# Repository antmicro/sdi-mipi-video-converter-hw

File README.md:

# SDI-MIPI Video Converter

Copyright (c) 2022-2025 [Antmicro](https://www.antmicro.com)

## Overview

This repository contains open hardware design files for a video accessory based on the [Lattice CrossLink-NX](https://www.latticesemi.com/Products/FPGAandCPLD/CrossLink-NX) FPGA which allows to connect multiple video streams from SDI or CSI inputs, process it on-board and export with CSI output.

The design files were prepared in KiCad 9.x.

## Repository structure

The main repository directory contains KiCad PCB project files, a [LICENSE](LICENSE), and a README.
The remaining files are stored in the following directories:

* `img` - contains graphics for this README

## Key Features

* LIFCL-40-9BG256C Lattice CrossLink-NX FPGA
* 3G SDI Input implemented with Semtech GS2971A deserializer 
* 3G SDI Loopback output implemented with Semtech GS2988 cable driver
* 3x4 CSI interfaces split 2/1 between two Antmicro 50-pin FFC connectors 
* 2Gbit (128Mx16) DDR3L DRAM

The board can be powered from either USB or Antmicro's 50-pin FFC connector.

Antmicro's 50-pin FFC connector is electrically compatible with several boards created by Antmicro, such as:
 
* [Jetson Nano/TX2 NX/Xavier NX Baseboard](https://github.com/antmicro/jetson-nano-baseboard)
* [OV9281 Dual Camera Board](https://github.com/antmicro/ov9281-camera-board)
* [HDMI-MIPI bridge](https://github.com/antmicro/hdmi-mipi-bridge)

## License

[Apache-2.0](LICENSE)

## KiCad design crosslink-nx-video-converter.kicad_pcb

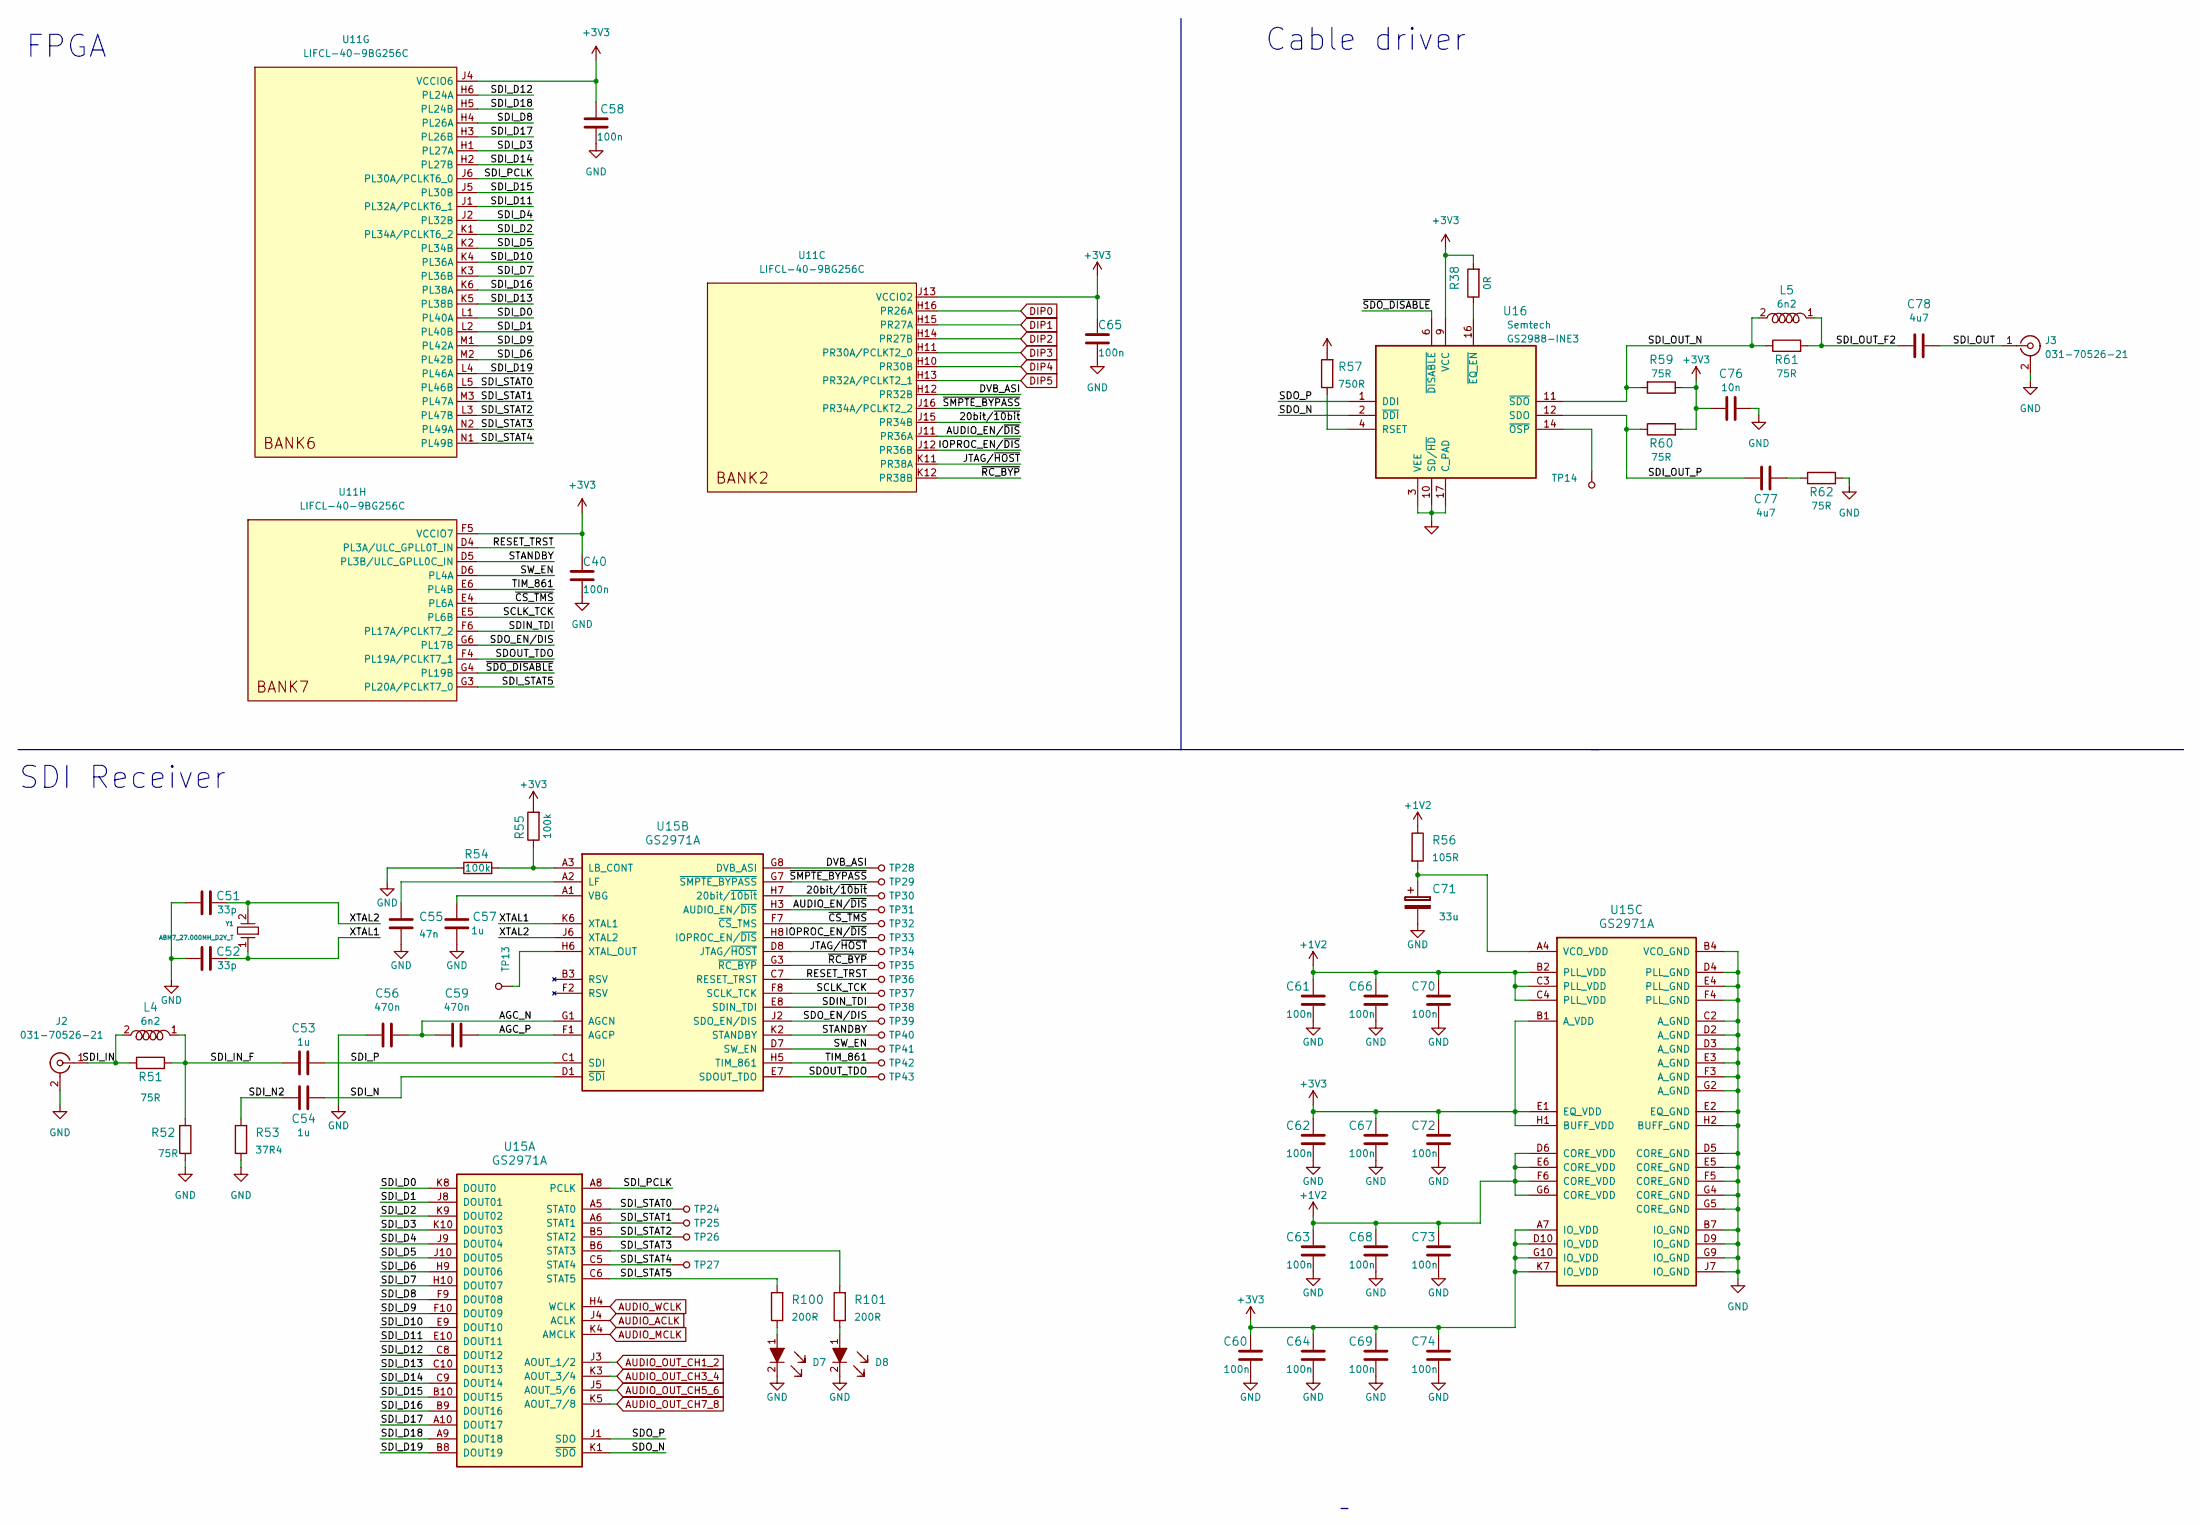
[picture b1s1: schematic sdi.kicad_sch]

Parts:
C40, C58, C60, C61, C62, C63, C64, C65, C66, C67, C68, C69, C70, C72, C73, C74: C_100n_0402; 0402-cap; MPN GRM155R61H104KE14D
C51, C52: C_33p_0402; 0402-cap; MPN MC0402N330J500CT
C53, C54, C57: C_1u_0402; 0402-cap; MPN C1005X6S1A105K050BC
C55: C_47n_0402; 0402-cap; MPN MC0402X473K160CT
C56, C59: C_470n_0402; 0402-cap; MPN C1005X5R1E474M050BB
C71: C_33u_0603; 0603-cap; MPN F980G336MMA
C76: C_10n_0402; 0402-cap; MPN 04025G103ZAT2A
C77, C78: C_4u7_0402; 0402-cap; MPN GRM155R61A475MEAAD
D7, D8: LTST-C190GKT; LED_0603; MPN LTST-C190GKT
J2, J3: 031-70526-21; BNC_Edge_Conn; MPN 031-70526-21
L4, L5: L_0402_6n2; 0402-cap; MPN LQW15AN6N2C00D
R38: R_0R_0402; 0402-res; MPN ERJ2GE0R00X
R51, R52, R59, R60, R61, R62: R_75R_0402; 0402-res; MPN RC0402FR-0775RL
R53: R_37R4_0402; 0402-res; MPN MCWR04X37R4FTL
R54, R55: R_100k_0402; 0402-res; MPN CRCW0402100KFKEDHP
R56: R_105R_0402; 0402-res; MPN MC00625W04021105R
R57: R_750R_0402; 0402-res; MPN RC0402FR-07750RL
R100, R101: R_200R_0603; 0603-res; MPN ERJ-UP3F2000V
TP13, TP14, TP24, TP25, TP26, TP27, TP28, TP29, TP30, TP31, TP32, TP33, TP34, TP35, TP36, TP37, TP38, TP39, TP40, TP41, TP42, TP43: TP_SMD_0_75MM; Testpoint_smd_0_75mm
U11: LIFCL-40-9BG256C; BGA-256_16x16_14.0x14.0mm; MPN LIFCL-40-9BG256C
U15: GS2971A; BGA100_11x11mm; MPN GS2971A
U16: GS2988; QFN-16_EP_4x4_Pitch0.65mm; MPN GS2988-INE3
Y1: ABM7_27.000MH_D2Y_T; ABM7_OSC; MPN ABM7-27.000MHZ-D2Y-T

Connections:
+1V2: C61.1, C63.1, C66.1, C68.1, C70.1, C73.1, R56.1, U15.B2 (PLL_VDD), U15.C3 (PLL_VDD), U15.C4 (PLL_VDD), U15.D6 (CORE_VDD), U15.E6 (CORE_VDD), U15.F6 (CORE_VDD), U15.G6 (CORE_VDD); also elsewhere on the board
/SDI/20bit/~10bit: TP30.1, U11.J15 (PR34B), U15.H7 (20bit/~10bit)
/SDI/AGC_N: C56.2, C59.1, U15.G1 (AGCN)
/SDI/AGC_P: C59.2, U15.F1 (AGCP)
/SDI/AUDIO_EN/~DIS: TP31.1, U11.J11 (PR36A), U15.H3 (AUDIO_EN/~DIS)
/SDI/DVB_ASI: TP28.1, U11.H12 (PR32B), U15.G8 (DVB_ASI)
/SDI/IOPROC_EN/~DIS: TP33.1, U11.J12 (PR36B), U15.H8 (IOPROC_EN/~DIS)
/SDI/JTAG/~HOST: TP34.1, U11.K11 (PR38A), U15.D8 (JTAG/~HOST)
/SDI/RESET_TRST: TP36.1, U11.D4 (PL3A/ULC_GPLL0T_IN), U15.C7 (RESET_TRST)
/SDI/SCLK_TCK: TP37.1, U11.E5 (PL6B), U15.F8 (SCLK_TCK)
/SDI/SDIN_TDI: TP38.1, U11.F6 (PL17A/PCLKT7_2), U15.E8 (SDIN_TDI)
/SDI/SDI_D0: U11.L1 (PL40A), U15.K8 (DOUT0)
/SDI/SDI_D1: U11.L2 (PL40B), U15.J8 (DOUT01)
/SDI/SDI_D2: U11.K1 (PL34A/PCLKT6_2), U15.K9 (DOUT02)
/SDI/SDI_D3: U11.H1 (PL27A), U15.K10 (DOUT03)
/SDI/SDI_D4: U11.J2 (PL32B), U15.J9 (DOUT04)
/SDI/SDI_D5: U11.K2 (PL34B), U15.J10 (DOUT05)
/SDI/SDI_D6: U11.M2 (PL42B), U15.H9 (DOUT06)
/SDI/SDI_D7: U11.K3 (PL36B), U15.H10 (DOUT07)
/SDI/SDI_D8: U11.H4 (PL26A), U15.F9 (DOUT08)
/SDI/SDI_D9: U11.M1 (PL42A), U15.F10 (DOUT09)
/SDI/SDI_D10: U11.K4 (PL36A), U15.E9 (DOUT10)
/SDI/SDI_D11: U11.J1 (PL32A/PCLKT6_1), U15.E10 (DOUT11)
/SDI/SDI_D12: U11.H6 (PL24A), U15.C8 (DOUT12)
/SDI/SDI_D13: U11.K5 (PL38B), U15.C10 (DOUT13)
/SDI/SDI_D14: U11.H2 (PL27B), U15.C9 (DOUT14)
/SDI/SDI_D15: U11.J5 (PL30B), U15.B10 (DOUT15)
/SDI/SDI_D16: U11.K6 (PL38A), U15.B9 (DOUT16)
/SDI/SDI_D17: U11.H3 (PL26B), U15.A10 (DOUT17)
/SDI/SDI_D18: U11.H5 (PL24B), U15.A9 (DOUT18)
/SDI/SDI_D19: U11.L4 (PL46A), U15.B8 (DOUT19)
/SDI/SDI_IN: J2.1 (In), L4.2, R51.1
/SDI/SDI_IN_F: C53.1, L4.1, R51.2, R52.2
/SDI/SDI_N: C54.2, U15.D1 (~SDI)
/SDI/SDI_N2: C54.1, R53.2
/SDI/SDI_OUT: C78.2, J3.1 (In)
/SDI/SDI_OUT_F2: C78.1, L5.1, R61.2
/SDI/SDI_OUT_N: L5.2, R59.2, R61.1, U16.11 (~SDO)
/SDI/SDI_OUT_P: C77.1, R60.1, U16.12 (SDO)
/SDI/SDI_P: C53.2, U15.C1 (SDI)
/SDI/SDI_PCLK: U11.J6 (PL30A/PCLKT6_0), U15.A8 (PCLK)
/SDI/SDI_STAT0: TP24.1, U11.L5 (PL46B), U15.A5 (STAT0)
/SDI/SDI_STAT1: TP25.1, U11.M3 (PL47A), U15.A6 (STAT1)
/SDI/SDI_STAT2: TP26.1, U11.L3 (PL47B), U15.B5 (STAT2)
/SDI/SDI_STAT3: R101.2, U11.N2 (PL49A), U15.B6 (STAT3)
/SDI/SDI_STAT4: TP27.1, U11.N1 (PL49B), U15.C5 (STAT4)
/SDI/SDI_STAT5: R100.2, U11.G3 (PL20A/PCLKT7_0), U15.C6 (STAT5)
/SDI/SDOUT_TDO: TP43.1, U11.F4 (PL19A/PCLKT7_1), U15.E7 (SDOUT_TDO)
/SDI/SDO_EN/DIS: TP39.1, U11.G6 (PL17B), U15.J2 (SDO_EN/DIS)
/SDI/SDO_N: U15.K1 (~SDO), U16.2 (~DDI)
/SDI/SDO_P: U15.J1 (SDO), U16.1 (DDI)
/SDI/STANDBY: TP40.1, U11.D5 (PL3B/ULC_GPLL0C_IN), U15.K2 (STANDBY)
/SDI/SW_EN: TP41.1, U11.D6 (PL4A), U15.D7 (SW_EN)
/SDI/TIM_861: TP42.1, U11.E6 (PL4B), U15.H5 (TIM_861)
/SDI/~CS_TMS: TP32.1, U11.E4 (PL6A), U15.F7 (~CS_TMS)
/SDI/~RC_BYP: TP35.1, U11.K12 (PR38B), U15.G3 (~RC_BYP)
/SDI/~SDO_DISABLE: U11.G4 (PL19B), U16.6 (~DISABLE)
/SDI/~SMPTE_BYPASS: TP29.1, U11.J16 (PR34A/PCLKT2_2), U15.G7 (~SMPTE_BYPASS)
AUDIO_ACLK: U15.J4 (ACLK); also elsewhere on the board
AUDIO_MCLK: U15.K4 (AMCLK); also elsewhere on the board
AUDIO_OUT_CH1_2: U15.J3 (AOUT_1/2); also elsewhere on the board
AUDIO_OUT_CH3_4: U15.K3 (AOUT_3/4); also elsewhere on the board
AUDIO_OUT_CH5_6: U15.J5 (AOUT_5/6); also elsewhere on the board
AUDIO_OUT_CH7_8: U15.K5 (AOUT_7/8); also elsewhere on the board
AUDIO_WCLK: U15.H4 (WCLK); also elsewhere on the board
DIP0: U11.H16 (PR26A); also elsewhere on the board
DIP1: U11.H15 (PR27A); also elsewhere on the board
DIP2: U11.H14 (PR27B); also elsewhere on the board
DIP3: U11.H11 (PR30A/PCLKT2_0); also elsewhere on the board
DIP4: U11.H10 (PR30B); also elsewhere on the board
DIP5: U11.H13 (PR32A/PCLKT2_1); also elsewhere on the board
unnamed: C55.1, U15.A2 (LF)
unnamed: C57.2, U15.A1 (VBG)
unnamed: C71.1, R56.2, U15.A4 (VCO_VDD)
unnamed: C77.2, R62.1
unnamed: D7.1, R100.1
unnamed: D8.1, R101.1
unnamed: R38.1, U16.16 (~EQ_EN)
unnamed: R54.2, R55.1, U15.A3 (LB_CONT)
unnamed: R57.1, U16.4 (RSET)
unnamed: TP13.1, U15.H6 (XTAL_OUT)
unnamed: TP14.1, U16.14 (~OSP)

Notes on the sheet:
Cable driver
FPGA
SDI Receiver

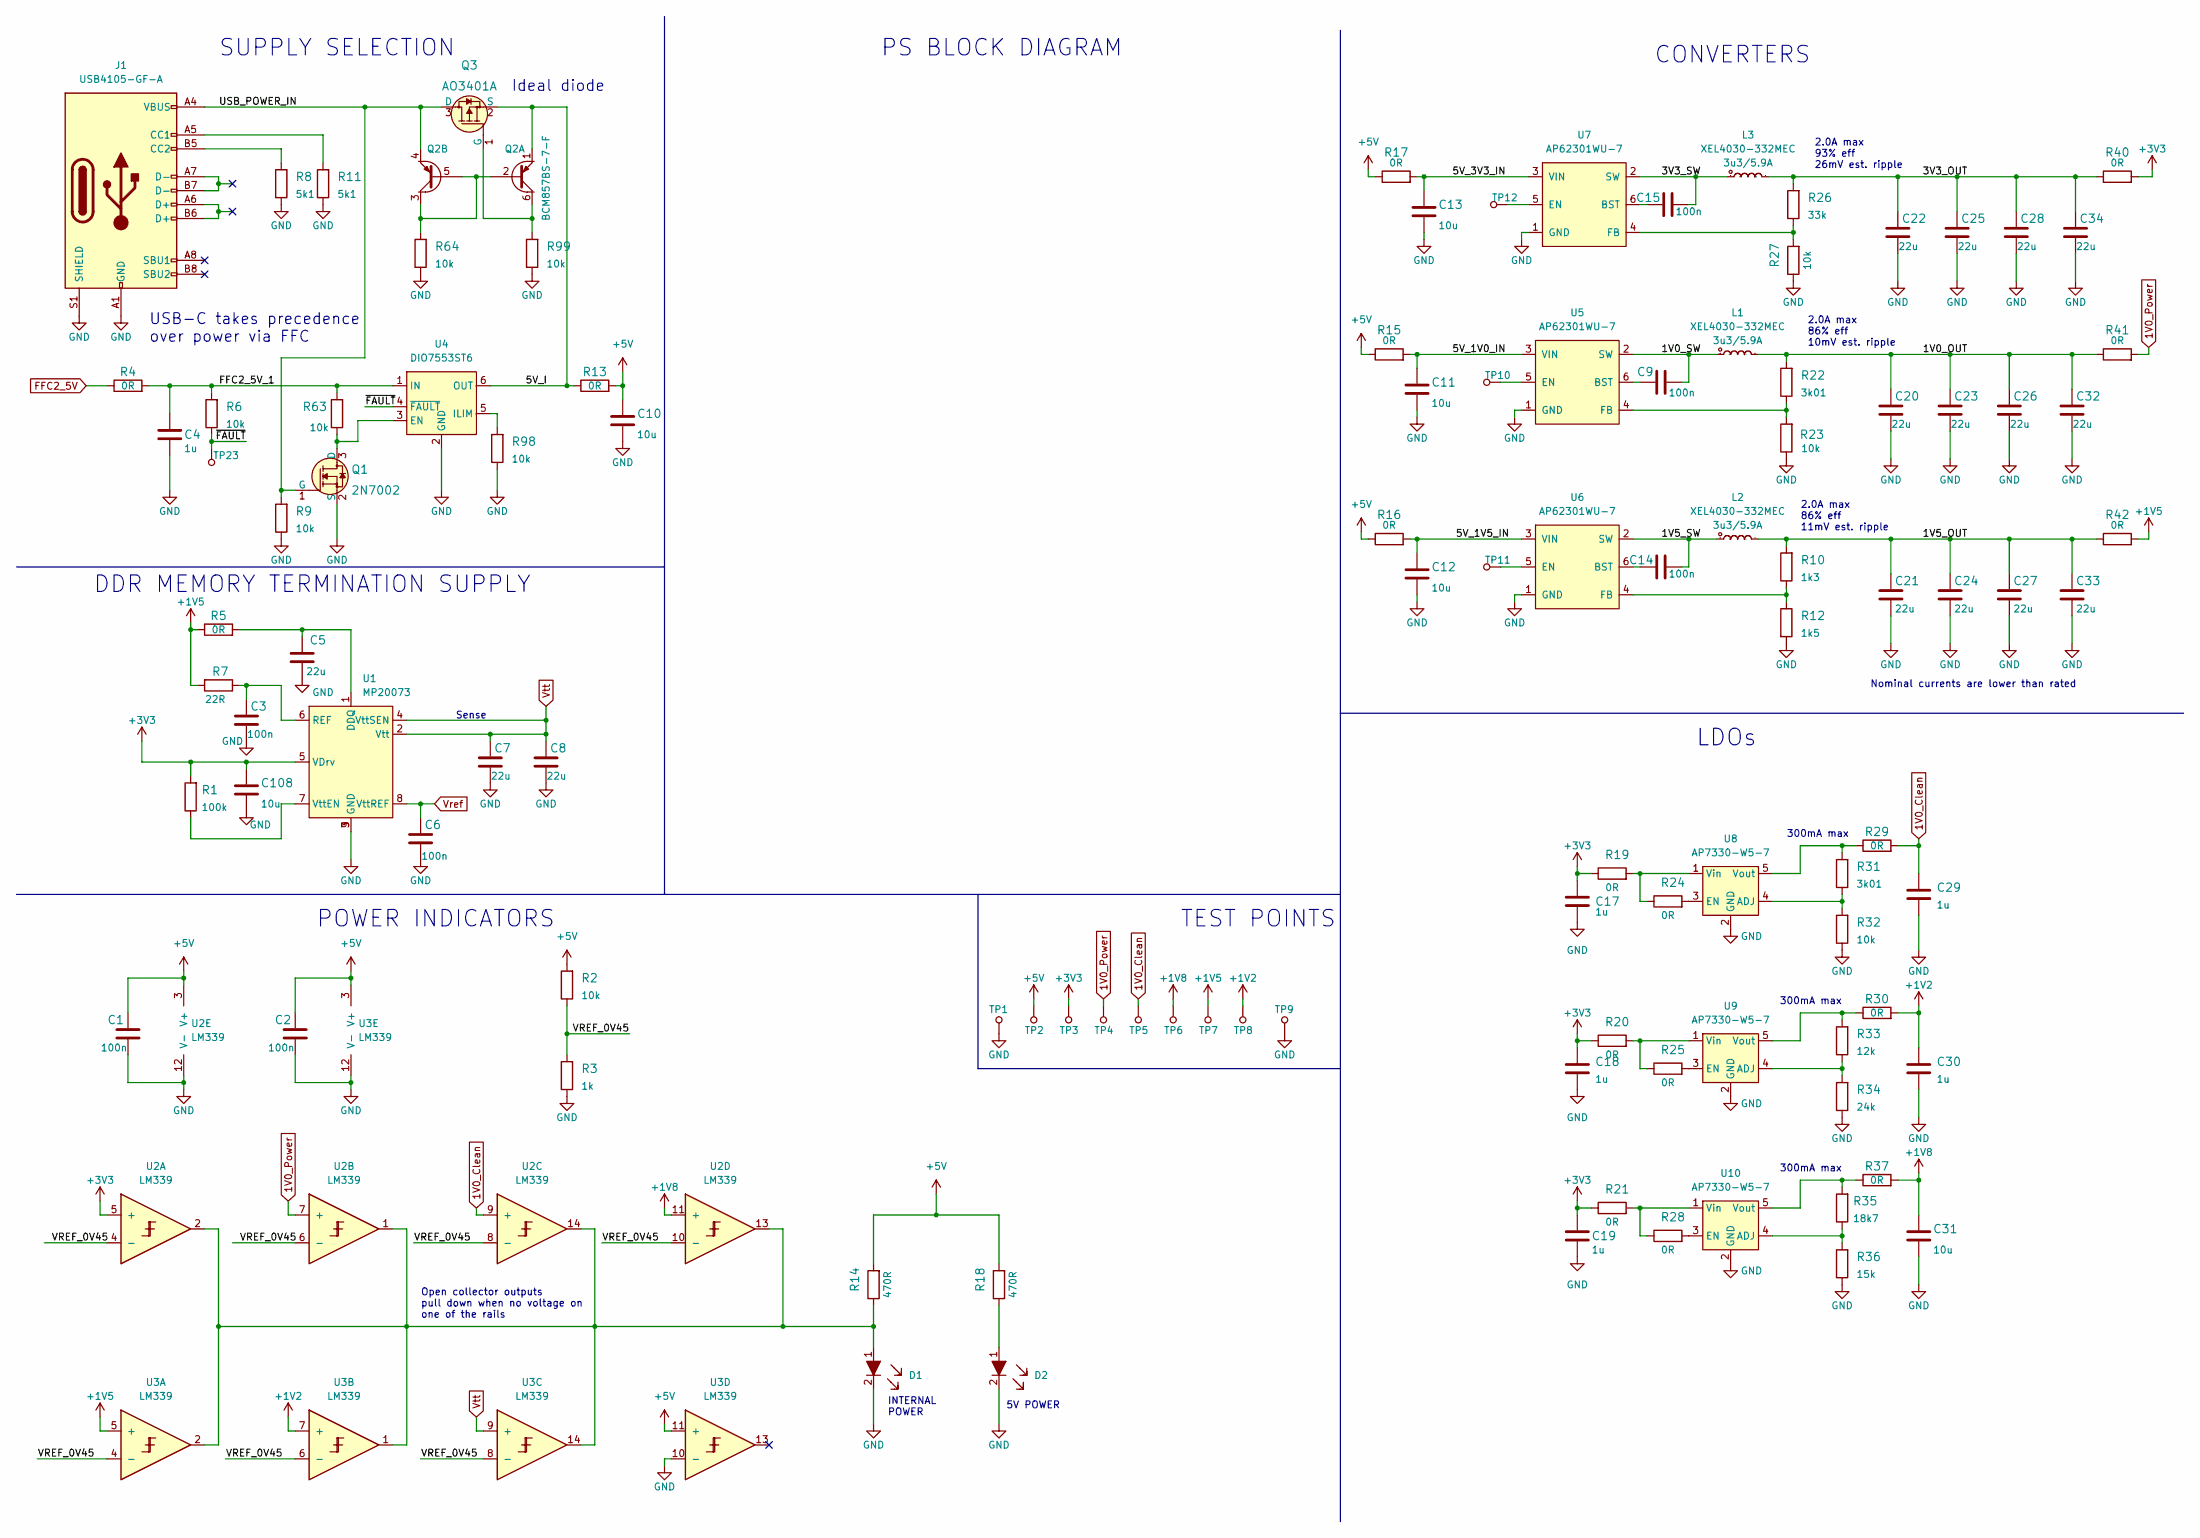
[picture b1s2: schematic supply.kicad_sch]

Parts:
C1, C2, C3, C6, C9, C14, C15: C_100n_0402; 0402-cap; MPN GRM155R61H104KE14D
C4, C17, C18, C19, C29, C30: C_1u_0603; 0603-cap; MPN 0603YD105KAT2A
C5, C7, C8, C20, C21, C22, C23, C24, C25, C26, C27, C28, C32, C33, C34: C_22u_0603; 0603-cap; MPN GRM188R60J226MEA0D
C10, C11, C12, C13, C31, C108: C_10u_0603; 0603-cap; MPN GRM188R61A106KE69D
D1, D2: LTST-C190GKT; LED_0603; MPN LTST-C190GKT
J1: USB4105-GF-A; GCT_USB4105-GF-A; MPN USB4105-GF-A
L1, L2, L3: XEL4030-332MEC; Coilcraft-XEL4030; MPN XEL4030-332MEC
Q1: 2N7002; SOT-23-3; MPN 2N7002
Q2: BCM857BS-7-F; SOT-363; MPN BCM857BS-7-F
Q3: AO3401A; SOT-23-3; MPN AO3401A
R1: R_100k_0402; 0402-res; MPN CRCW0402100KFKEDHP
R2, R6, R9, R23, R27, R32, R63, R64, R98, R99: R_10k_0402; 0402-res; MPN CRCW040210K0FKEDHP
R3: R_1k_0402; 0402-res; MPN CR0402-FX-1001GLF
R4, R13: R_0R_1206; 1206-res; MPN MCMR12X000_PTL
R5, R15, R16, R17, R40, R41, R42: R_0R_0805; 0805-res; MPN CRCW08050000Z0EA
R7: R_22R_0402; 0402-res; MPN CRCW040222R0FKED
R8, R11: R_5k1_0402; 0402-res; MPN SFR01MZPJ512
R10: R_1k3_0402; 0402-res; MPN CR0402-FX-1301GLF
R12: R_1k5_0402; 0402-res; MPN MP000515
R14, R18: R_470R_0402; 0402-res; MPN CRCW0402470RFKED
R19, R20, R21, R24, R25, R28: R_0R_0402; 0402-res; MPN ERJ2GE0R00X
R22, R31: R_3k01_0402; 0402-res; MPN CRCW04023K01FKED
R26: R_33k_0402; 0402-res; MPN RC0402FR-0733KL
R29, R30, R37: R_0R_0603; 0603-res; MPN CR0603-J/-000ELF
R33: R_12k_0402; 0402-res; MPN CRCW040212K0FKEDHP
R34: R_24k_0402; 0402-res; MPN ERJ2RKF2402X
R35: R_18k7_0402; 0402-res; MPN CR0402-FX-1872GLF
R36: R_15k_0402; 0402-res; MPN SFR01MZPF1502
TP1, TP2, TP3, TP4, TP5, TP6, TP7, TP8, TP9, TP10, TP11, TP12, TP23: TP_SMD_0_75MM; Testpoint_smd_0_75mm
U1: MP20073; MSOP-8-1EP_W3mm; MPN MP20073DH-LF-P
U2, U3: LM339; TSSOP-14_4.4x5mm_P0.65mm; MPN LM339PT
U4: DIO7553ST6; SOT23-6L; MPN DIO7553ST6
U5, U6, U7: AP62301WU-7; TSOT23-6; MPN AP62301WU-7
U8, U9, U10: AP7330-W5-7; SOT-23-5; MPN AP7330-W5-7

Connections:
1V0_Clean: C29.1, R29.2, TP5.1, U2.9 (+)
+1V2: C30.1, R30.2, TP8.1, U3.7 (+); also elsewhere on the board
+1V5: R5.1, R7.2, R42.2, TP7.1, U3.5 (+); also elsewhere on the board
+5V: C1.1, C2.1, C10.1, R2.2, R13.2, R14.2, R15.1, R16.1, R17.1, R18.2, TP2.1, U2.3 (V+), U3.3 (V+), U3.11 (+); also elsewhere on the board
/Power Supply/1V0_IN: C11.1, R15.2, U5.3 (VIN)
/Power Supply/1V0_OUT: C20.1, C23.1, C26.1, C32.1, L1.2, R22.2, R41.1
/Power Supply/1V0_SW: C9.2, L1.1, U5.2 (SW)
/Power Supply/1V5_IN: C12.1, R16.2, U6.3 (VIN)
/Power Supply/1V5_OUT: C21.1, C24.1, C27.1, C33.1, L2.2, R10.2, R42.1
/Power Supply/1V5_SW: C14.2, L2.1, U6.2 (SW)
/Power Supply/3V3_IN: C13.1, R17.2, U7.3 (VIN)
/Power Supply/3V3_OUT: C22.1, C25.1, C28.1, C34.1, L3.2, R26.2, R40.1
/Power Supply/3V3_SW: C15.2, L3.1, U7.2 (SW)
/Power Supply/VREF_0V45: R2.1, R3.2, U2.4 (-), U2.6 (-), U2.8 (-), U2.10 (-), U3.4 (-), U3.6 (-), U3.8 (-)
/Power Supply/~FAULT: R6.1, TP23.1, U4.4 (~FAULT)
FFC2_5V: R4.1; also elsewhere on the board
unnamed: C3.2, R7.1, U1.6 (REF)
unnamed: C5.1, R5.2, U1.1 (DDQ)
unnamed: C9.1, U5.6 (BST)
unnamed: C14.1, U6.6 (BST)
unnamed: C15.1, U7.6 (BST)
unnamed: D1.1, R14.1, U2.1, U2.2, U2.13, U2.14, U3.1, U3.2, U3.14
unnamed: D2.1, R18.1
unnamed: Q2.1, Q3.2 (S), R13.1, U4.6 (OUT)
unnamed: Q2.2, Q2.3, Q2.5, R64.2
unnamed: Q2.6, Q3.1 (G), R99.2
unnamed: R1.1, U1.7 (VttEN)
unnamed: R10.1, R12.1, U6.4 (FB)
unnamed: R19.2, R24.1, U8.1 (Vin)
unnamed: R20.2, R25.1, U9.1 (Vin)
unnamed: R21.2, R28.1, U10.1 (Vin)
unnamed: R22.1, R23.2, U5.4 (FB)
unnamed: R24.2, U8.3 (EN)
unnamed: R25.2, U9.3 (EN)
unnamed: R26.1, R27.2, U7.4 (FB)
unnamed: R28.2, U10.3 (EN)
unnamed: R29.1, R31.2, U8.5 (Vout)
unnamed: R30.1, R33.2, U9.5 (Vout)
unnamed: R31.1, R32.2, U8.4 (ADJ)
unnamed: R33.1, R34.2, U9.4 (ADJ)
unnamed: R35.1, R36.2, U10.4 (ADJ)
unnamed: R35.2, R37.1, U10.5 (Vout)
unnamed: R98.2, U4.5 (ILIM)
unnamed: TP10.1, U5.5 (EN)
unnamed: TP11.1, U6.5 (EN)
unnamed: TP12.1, U7.5 (EN)
Vref: C6.2, U1.8 (VttREF); also elsewhere on the board
Vtt: C7.1, C8.1, U1.2 (Vtt), U1.4 (VttSEN), U3.9 (+); also elsewhere on the board

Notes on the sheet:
DDR MEMORY TERMINATION SUPPLY
300mA max
INTERNAL POWER
LDOs
Ideal diode
2.0A max 86% eff 11mV est. ripple
Nominal currents are lower than rated
2.0A max 93% eff 26mV est. ripple
Sense
SUPPLY SELECTION
Open collector outputs pull down when no voltage on one of the rails
CONVERTERS
5V POWER
USB-C takes precedence over power via FFC
PS BLOCK DIAGRAM
TEST POINTS
2.0A max 86% eff 10mV est. ripple
POWER INDICATORS

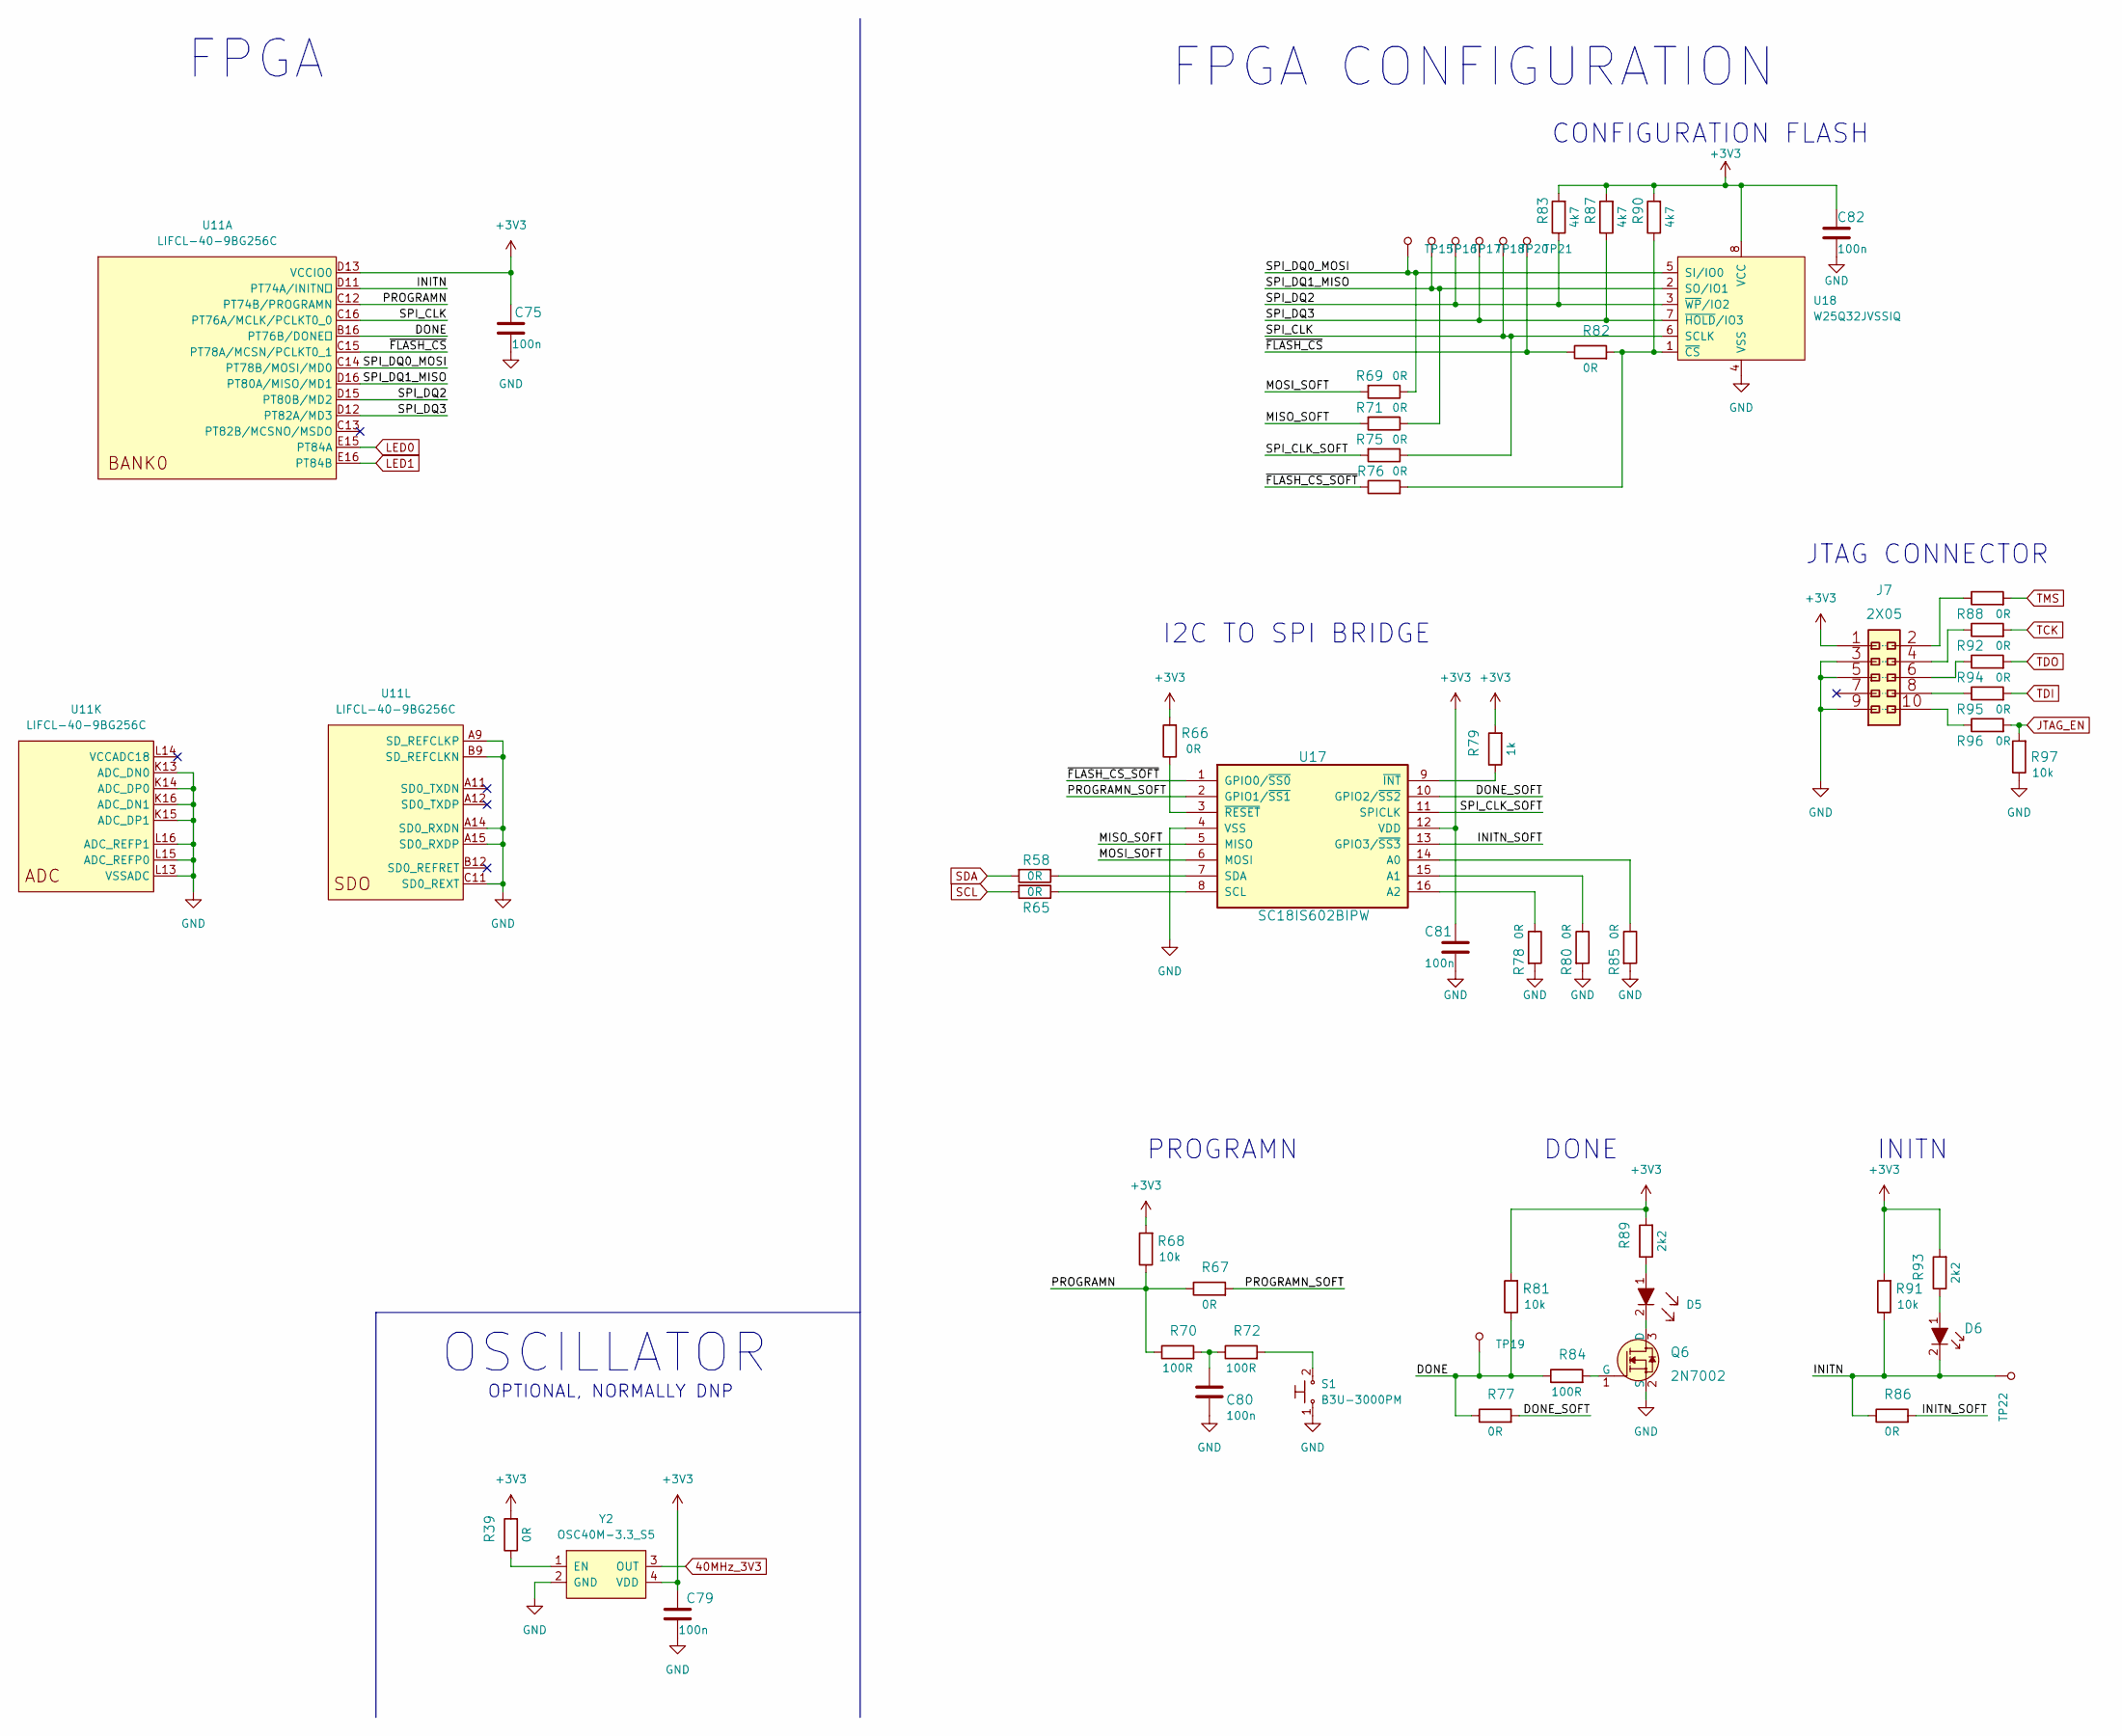
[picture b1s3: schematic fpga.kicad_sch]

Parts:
C75, C79, C80, C81, C82: C_100n_0402; 0402-cap; MPN GRM155R61H104KE14D
D5: LTST-C190GKT; LED_0603; MPN LTST-C190GKT
D6: LTST-C190KRKT; LED_0603; MPN LTST-C190KRKT
J7: 2X05; SHF-105-01-X-D-SM; MPN SHF-105-01-L-D-SM
Q6: 2N7002; SOT-23-3; MPN 2N7002
R39, R66, R67, R69, R71, R75, R76, R77, R78, R80, R82, R85, R86, R88, R92, R94, R95, R96: R_0R_0402; 0402-res; MPN ERJ2GE0R00X
R58, R65: R_0R_0402; 0603-res; MPN CR0603-J/-000ELF
R68, R81, R91, R97: R_10k_0402; 0402-res; MPN CRCW040210K0FKEDHP
R70, R72, R84: R_100R_0402; 0402-res; MPN CR0402-FX-1000GLF
R79: R_1k_0402; 0402-res; MPN CR0402-FX-1001GLF
R83, R87, R90: R_4k7_0402; 0402-res; MPN MCS04020C4701FE000
R89, R93: R_2k2_0402; 0402-res; MPN RC0402FR-072K2L
S1: B3U-3000PM; B3U-3000P; MPN B3U-3000PM
TP15, TP16, TP17, TP18, TP19, TP20, TP21, TP22: TP_SMD_0_75MM; Testpoint_smd_0_75mm
U11: LIFCL-40-9BG256C; BGA-256_16x16_14.0x14.0mm; MPN LIFCL-40-9BG256C
U17: SC18IS602BIPW; SC18IS602B; MPN SC18IS602BIPW
U18: W25Q32JVSSIQ; SOIC-8_W5.3mm; MPN W25Q32JVSSIQ
Y2: OSC40M-3.3_S5; OSC-4_5.0x3.2mm; MPN OSC40M-3.3/S5

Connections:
40MHz_3V3: Y2.3 (OUT); also elsewhere on the board
/FPGA/DONE: R77.1, R81.1, R84.1, TP19.1, U11.B16 (PT76B/DONE)
/FPGA/DONE_SOFT: R77.2, U17.10 (GPIO2/~SS2)
/FPGA/INITN: D6.2, R86.1, R91.1, TP22.1, U11.D11 (PT74A/INITN)
/FPGA/INITN_SOFT: R86.2, U17.13 (GPIO3/~SS3)
/FPGA/MISO_SOFT: R71.2, U17.5 (MISO)
/FPGA/MOSI_SOFT: R69.2, U17.6 (MOSI)
/FPGA/PROGRAMN: R67.1, R68.1, R70.1, U11.C12 (PT74B/PROGRAMN)
/FPGA/PROGRAMN_SOFT: R67.2, U17.2 (GPIO1/~SS1)
/FPGA/SPI_CLK: R75.1, TP20.1, U11.C16 (PT76A/MCLK/PCLKT0_0), U18.6 (SCLK)
/FPGA/SPI_CLK_SOFT: R75.2, U17.11 (SPICLK)
/FPGA/SPI_DQ0_MOSI: R69.1, TP15.1, U11.C14 (PT78B/MOSI/MD0), U18.5 (SI/IO0)
/FPGA/SPI_DQ1_MISO: R71.1, TP16.1, U11.D16 (PT80A/MISO/MD1), U18.2 (SO/IO1)
/FPGA/SPI_DQ2: R83.1, TP17.1, U11.D15 (PT80B/MD2), U18.3 (~WP/IO2); also elsewhere on the board
/FPGA/SPI_DQ3: R87.1, TP18.1, U11.D12 (PT82A/MD3), U18.7 (~HOLD/IO3); also elsewhere on the board
/FPGA/~FLASH_CS_SOFT: R76.1, U17.1 (GPIO0/~SS0)
/FPGA/~FLASH_CS: R82.1, TP21.1, U11.C15 (PT78A/MCSN/PCLKT0_1)
JTAG_EN: R96.2, R97.2; also elsewhere on the board
LED0: U11.E15 (PT84A); also elsewhere on the board
LED1: U11.E16 (PT84B); also elsewhere on the board
unnamed: C80.1, R70.2, R72.1
unnamed: D5.1, R89.1
unnamed: D5.2, Q6.3 (D)
unnamed: D6.1, R93.1
unnamed: J7.2, R88.1
unnamed: J7.4, R92.1
unnamed: J7.6, R94.1
unnamed: J7.8, R95.1
unnamed: J7.10, R96.1
unnamed: Q6.1 (G), R84.2
unnamed: R39.1, Y2.1 (EN)
unnamed: R58.1, U17.7 (SDA)
unnamed: R65.1, U17.8 (SCL)
unnamed: R66.1, U17.3 (~RESET)
unnamed: R72.2, S1.2
unnamed: R76.2, R82.2, R90.1, U18.1 (~CS)
unnamed: R78.1, U17.16 (A2)
unnamed: R79.1, U17.9 (~INT)
unnamed: R80.1, U17.15 (A1)
unnamed: R85.1, U17.14 (A0)
SCL: R65.2; also elsewhere on the board
SDA: R58.2; also elsewhere on the board
TCK: R92.2; also elsewhere on the board
TDI: R95.2; also elsewhere on the board
TDO: R94.2; also elsewhere on the board
TMS: R88.2; also elsewhere on the board

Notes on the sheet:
DONE
FPGA
OSCILLATOR
OPTIONAL, NORMALLY DNP
FPGA CONFIGURATION
JTAG CONNECTOR
CONFIGURATION FLASH
I2C TO SPI BRIDGE
INITN
PROGRAMN
